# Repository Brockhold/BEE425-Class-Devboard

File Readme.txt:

This repository hosts the schematic and layout files for a TIVA-C TM4C123G breakout board.
The board was designed for BEE425 at UW:B, during winter 2019.

On the board are footprints for the following devices:
1 TO-220 LM35DT analog temperature sensor
1 16DIP ULM2003A darlington transistor array
1 18DIP NTE3074 common-anode two digit 7-segment LED display
1 TO-220 TIP29A NPN power transistor
2 T0-92 2N 3906 transistors
-- As well as an assortment of current limiting resistors, a protection diode, and a filtering cap. See schematic for details.

The board also includes otherwise-unrelated programming headers for an 6SOIC and an 8SOIC, for example the ATTINY10 and MX25L1606EM2I-12G.

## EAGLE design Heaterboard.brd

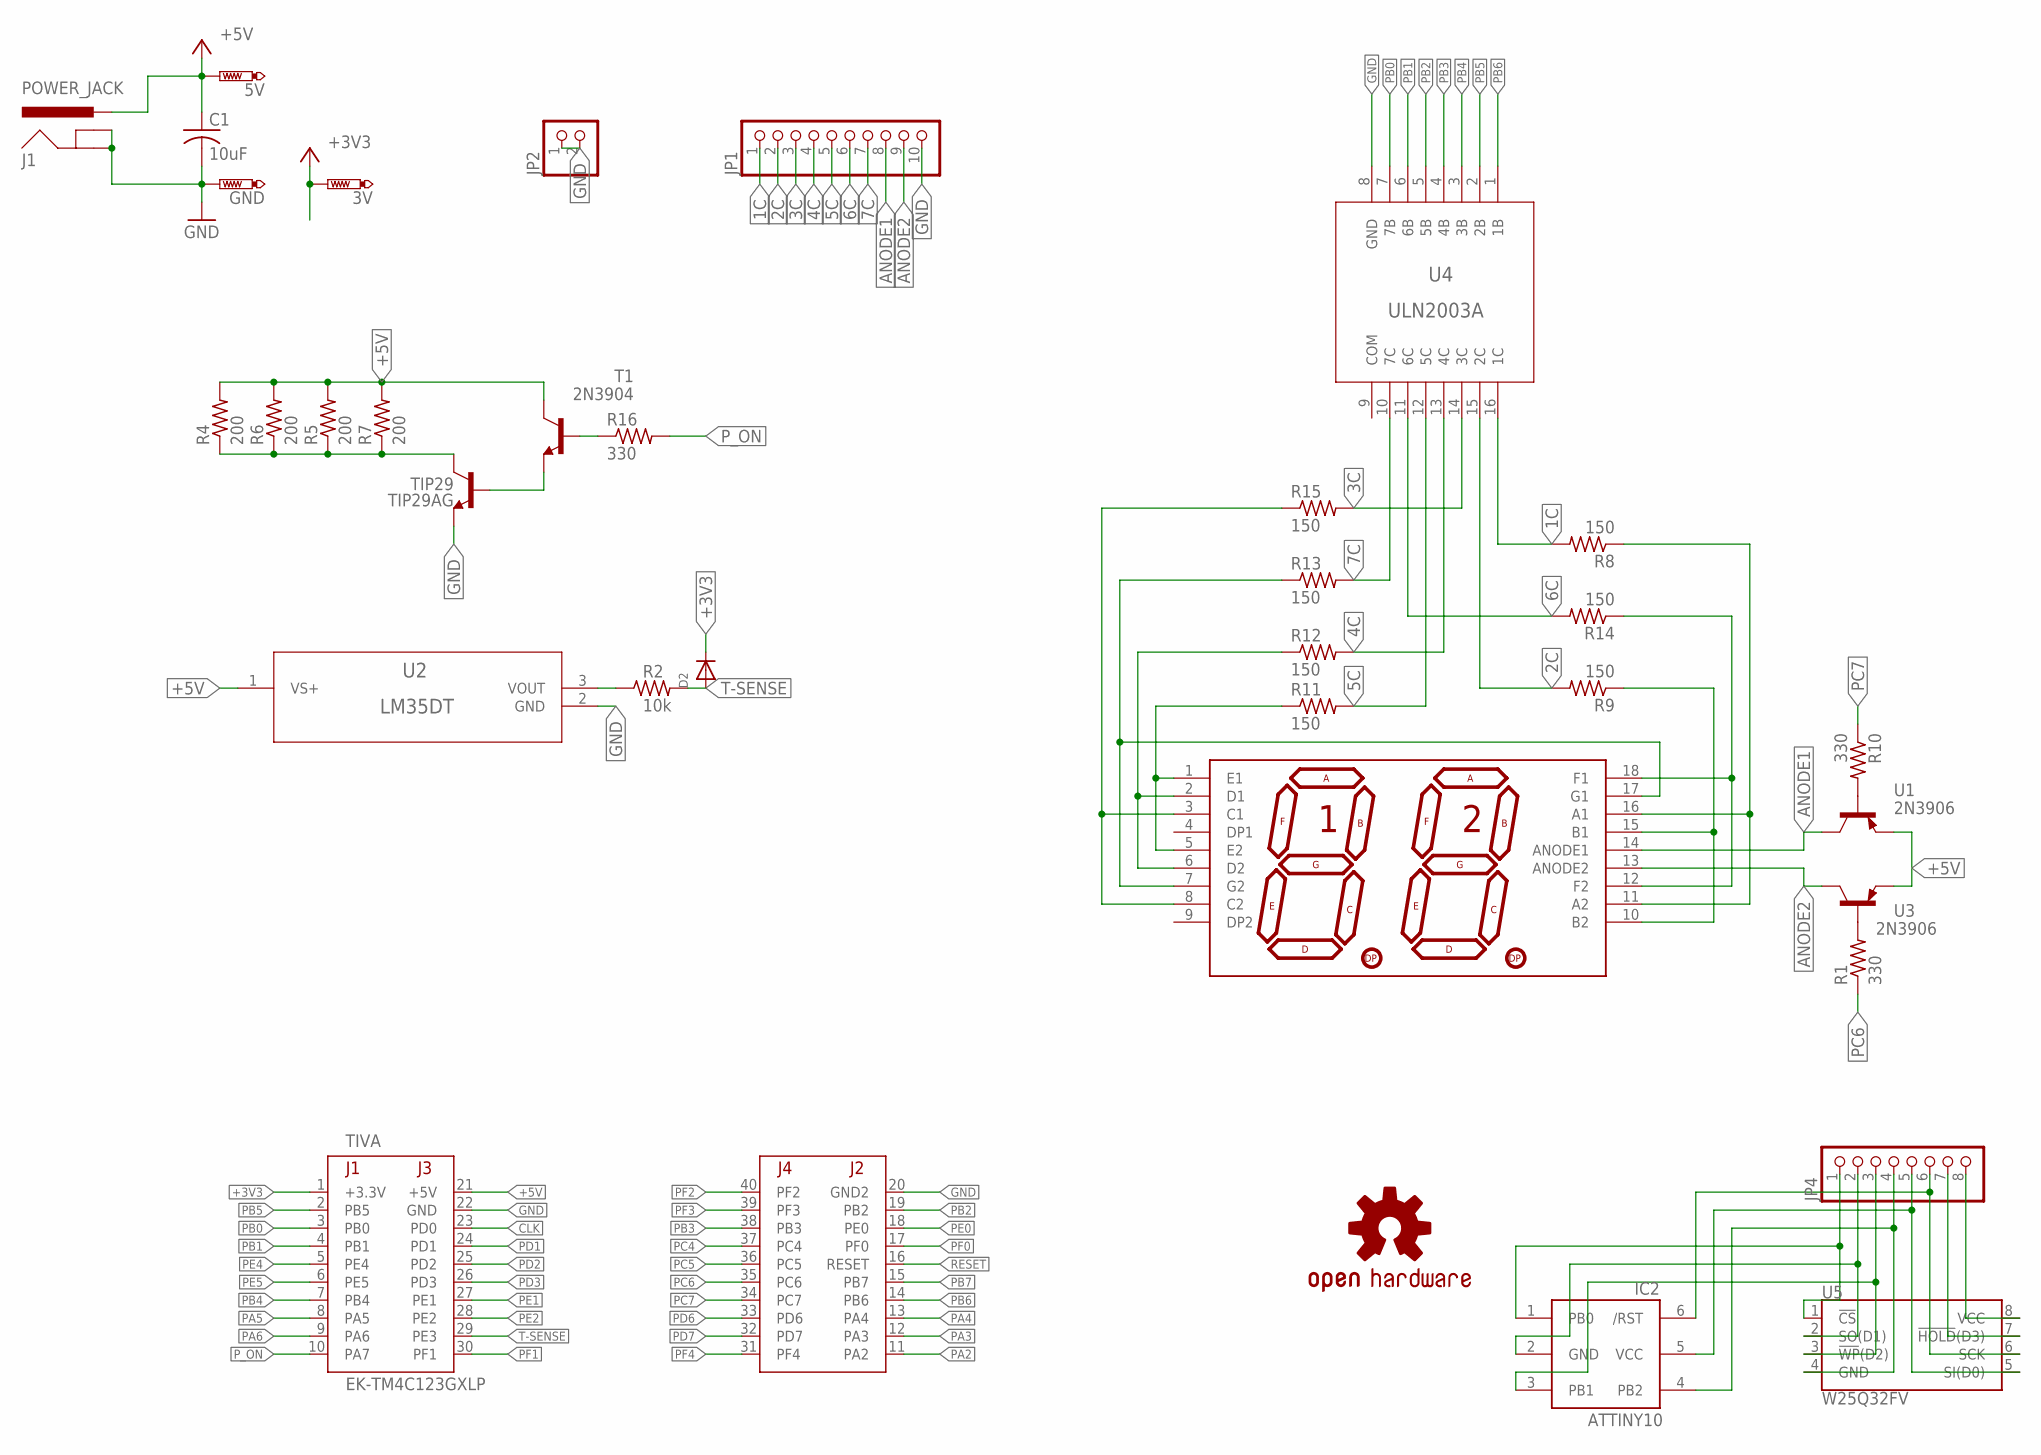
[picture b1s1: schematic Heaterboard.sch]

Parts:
3V, 5V: PTR1PAD1-13; P1-13
7SEG: NTE3074
C1: 10uF; C025-030X050
D2: DIODEDO-1N4148; DO-1N4148
GND: PTR1PAD1-13; P1-13
IC2: ATTINY10; SOT23-6
J1: POWER_JACK; POWER_JACK_PTH
JP1: PINHD-1X10/90; 1X10/90
JP2: PINHD-1X2; 1X02
JP4: PINHD-1X8; 1X08
LOGO1: OSHW-LOGOL; OSHW-LOGO-L
R1, R10, R16: 330; 0204/5
R2: 10k; 0204/5
R4, R5, R6, R7: 200; 0207/10
R8, R9, R11, R12, R13, R14, R15: 150; 0204/5
T1: 2N3904; TO92
TIP29: TIP29AG; TO220
TIVA: EK-TM4C123GXLP; TM4C123LAUNCHPAD
U1, U3: 2N3906; TO-92_2
U2: LM35DT; TA03F
U4: ULN2003A; DIP-16
U5: W25Q32FV; SOIC-8

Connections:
1C: JP1.1, R8.2, U4.16 (1C)
2C: JP1.2, R9.2, U4.15 (2C)
3C: JP1.3, R15.2, U4.14 (3C)
4C: JP1.4, R12.2, U4.13 (4C)
5C: JP1.5, R11.2, U4.12 (5C)
6C: JP1.6, R14.2, U4.11 (6C)
7C: JP1.7, R13.2, U4.10 (7C)
+3V3: 3V.TP, D2.C, TIVA.1 (+3.3V)
+5V: 5V.TP, C1.1, J1.PWR, R4.2, R5.2, R6.2, R7.2, T1.1 (C), TIVA.21 (+5V), U1.3 (E), U2.1 (VS+), U3.3 (E)
ANODE1: 7SEG.14 (ANODE1), JP1.8, U1.1 (C)
ANODE2: 7SEG.13 (ANODE2), JP1.9, U3.1 (C)
CLK: TIVA.23 (PD0)
GND: C1.2, GND.TP, J1.GND, J1.GNDBREAK, JP1.10, JP2.1, JP2.2, TIP29.3 (E), TIVA.20 (GND2), TIVA.22 (GND), U2.2 (GND), U4.8 (GND)
HEATER_COM: R4.1, R5.1, R6.1, R7.1, TIP29.2 (C)
unnamed: R2.1, U2.3 (VOUT)
unnamed: R16.1, T1.2 (B)
unnamed: T1.3 (E), TIP29.1 (B)
unnamed: R10.2, U1.2 (B)
unnamed: R1.2, U3.2 (B)
unnamed: 7SEG.11 (A2), 7SEG.16 (A1), R8.1
unnamed: IC2.4 (PB2), JP4.4, U5.4 (GND)
unnamed: 7SEG.10 (B2), 7SEG.15 (B1), R9.1
unnamed: 7SEG.3 (C1), 7SEG.8 (C2), R15.1
unnamed: 7SEG.2 (D1), 7SEG.6 (D2), R12.1
unnamed: 7SEG.1 (E1), 7SEG.5 (E2), R11.1
unnamed: 7SEG.12 (F2), 7SEG.18 (F1), R14.1
unnamed: 7SEG.7 (G2), 7SEG.17 (G1), R13.1
unnamed: IC2.1 (PB0), JP4.1, U5.1 (!CS!)
unnamed: IC2.2 (GND), JP4.2, U5.2 (SO(D1))
unnamed: IC2.3 (PB1), JP4.3, U5.3 (!WP!(D2))
unnamed: IC2.5 (VCC), JP4.5, U5.5 (SI(D0))
unnamed: IC2.6 (/RST), JP4.6, U5.6 (SCK)
unnamed: JP4.7, U5.7 (!HOLD!(D3))
unnamed: JP4.8, U5.8 (VCC)
PA2: TIVA.11 (PA2)
PA3: TIVA.12 (PA3)
PA4: TIVA.13 (PA4)
PA5: TIVA.8 (PA5)
PA6: TIVA.9 (PA6)
PB0: TIVA.3 (PB0), U4.7 (7B)
PB1: TIVA.4 (PB1), U4.6 (6B)
PB2: TIVA.19 (PB2), U4.5 (5B)
PB3: TIVA.38 (PB3), U4.4 (4B)
PB4: TIVA.7 (PB4), U4.3 (3B)
PB5: TIVA.2 (PB5), U4.2 (2B)
PB6: TIVA.14 (PB6), U4.1 (1B)
PB7: TIVA.15 (PB7)
PC4: TIVA.37 (PC4)
PC5: TIVA.36 (PC5)
PC6: R1.1, TIVA.35 (PC6)
PC7: R10.1, TIVA.34 (PC7)
PD1: TIVA.24 (PD1)
PD2: TIVA.25 (PD2)
PD3: TIVA.26 (PD3)
PD6: TIVA.33 (PD6)
PD7: TIVA.32 (PD7)
PE0: TIVA.18 (PE0)
PE1: TIVA.27 (PE1)
PE2: TIVA.28 (PE2)
PE4: TIVA.5 (PE4)
PE5: TIVA.6 (PE5)
PF0: TIVA.17 (PF0)
PF1: TIVA.30 (PF1)
PF2: TIVA.40 (PF2)
PF3: TIVA.39 (PF3)
PF4: TIVA.31 (PF4)
P_ON: R16.2, TIVA.10 (PA7)
RESET: TIVA.16 (RESET)
T-SENSE: D2.A, R2.2, TIVA.29 (PE3)

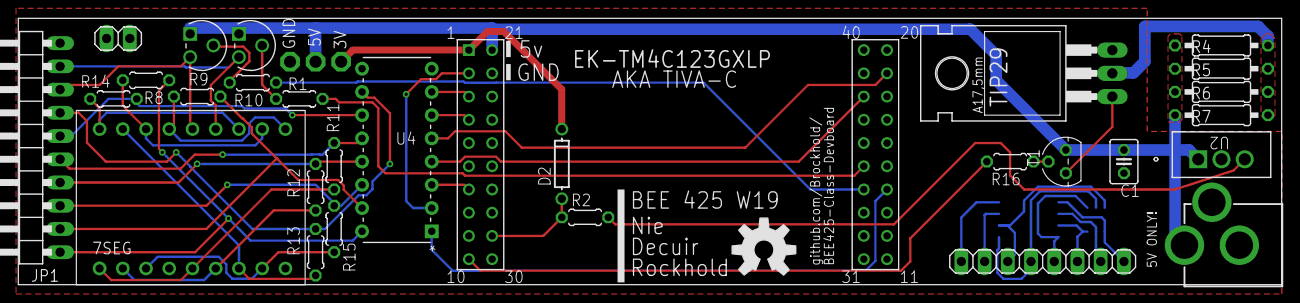
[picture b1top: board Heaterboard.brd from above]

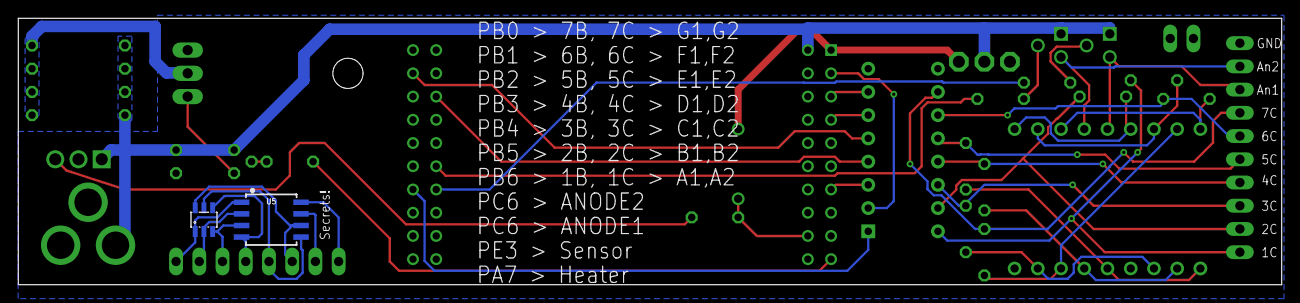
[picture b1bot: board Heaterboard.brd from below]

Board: 2 copper layers, 138.2 x 29.1 mm, 35 parts (2 on the bottom side), 44 nets.

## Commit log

2019-02-25 initiial
2019-02-26 checkpoint for schematic capture
2019-03-01 checkpoint before massive rework
2019-03-01 manually created NTE3074
2019-03-05 final checkpoint
2019-03-05 Added readme, because this repo looks a bit empty
2019-03-05 Added Eagle project file, for convenience
2019-03-05 Added link to this guthub repo
2019-03-14 corrected reversed LM35

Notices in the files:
parts and their libraries:
SparkFun-Aesthetics: Licensing: Creative Commons ShareAlike 4.0 International - https://creativecommons.org/licenses/by-sa/4.0
